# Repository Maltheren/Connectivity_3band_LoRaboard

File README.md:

# Connectivity_3band_LoRaboard
The first revision lora testboards for the tunnel measurement project

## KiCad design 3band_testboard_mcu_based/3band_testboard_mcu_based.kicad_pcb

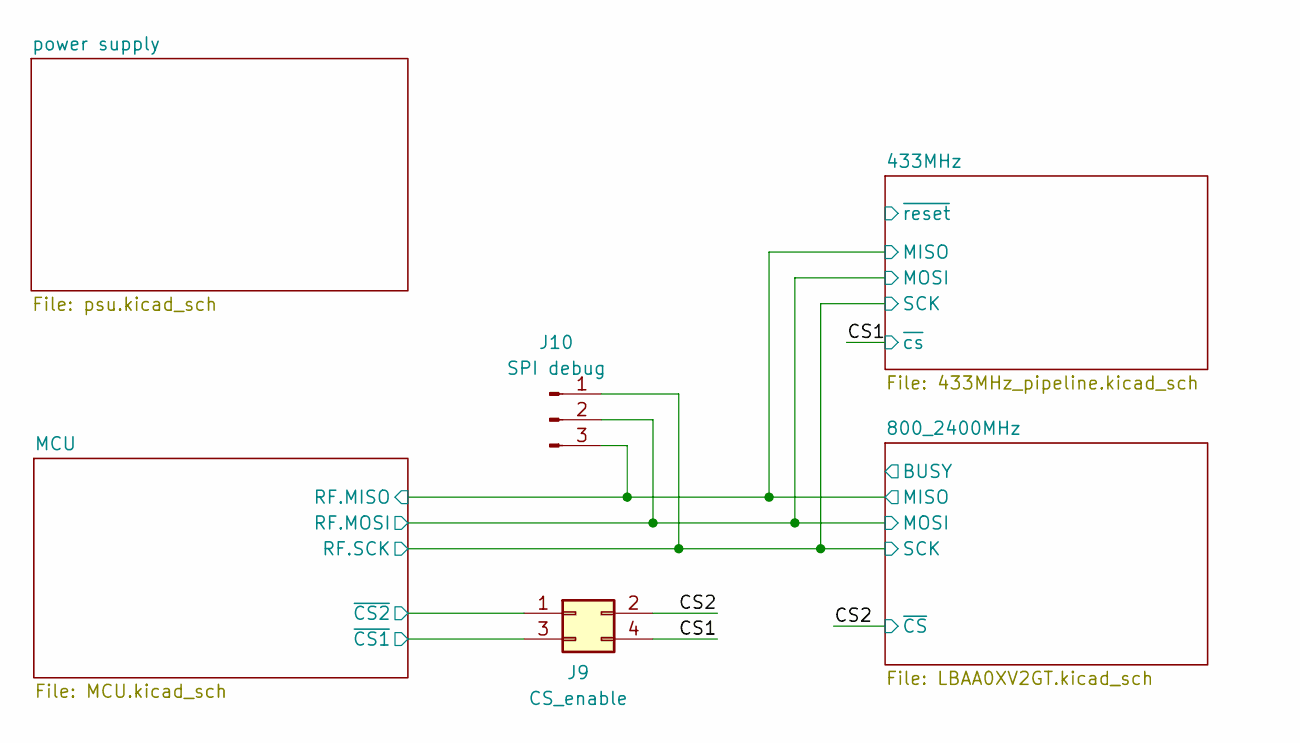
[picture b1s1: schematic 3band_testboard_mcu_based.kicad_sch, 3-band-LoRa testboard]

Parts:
J9: CS_enable; PinHeader_2x02_P2.54mm_Vertical
J10: SPI debug; PinHeader_1x03_P2.54mm_Vertical

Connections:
/433MHz/MISO: J10.3; also elsewhere on the board
/433MHz/MOSI: J10.2; also elsewhere on the board
/433MHz/SCK: J10.1; also elsewhere on the board
/CS1: J9.4; also elsewhere on the board
/CS2: J9.2; also elsewhere on the board
/MCU/~CS1: J9.3; also elsewhere on the board
/MCU/~CS2: J9.1; also elsewhere on the board

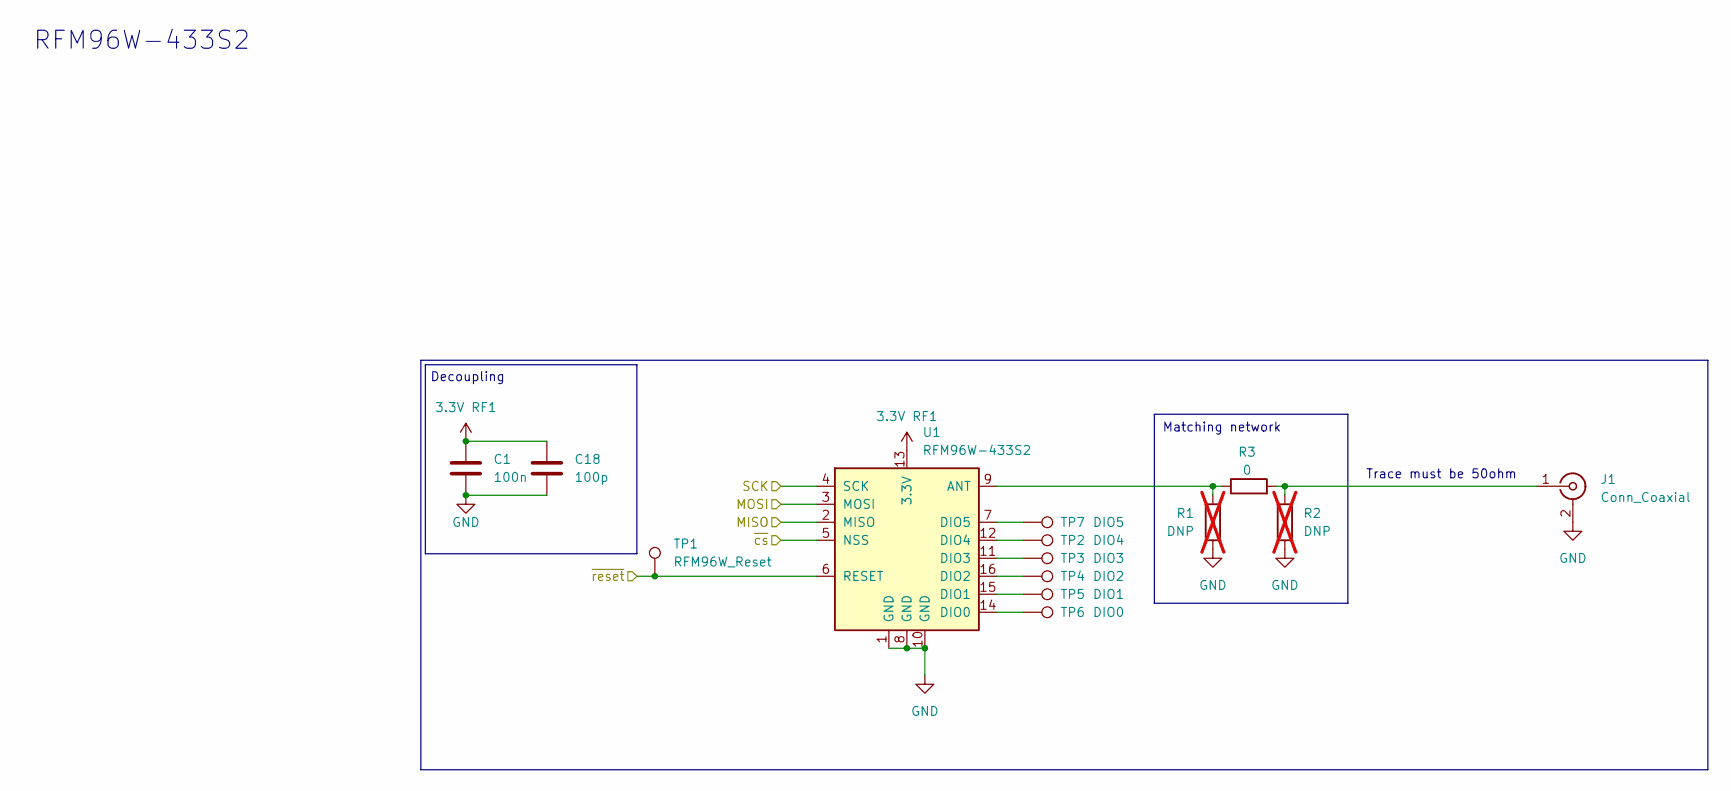
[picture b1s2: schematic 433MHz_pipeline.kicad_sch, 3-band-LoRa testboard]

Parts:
C1: 100n; C_0603_1608Metric_Pad1.08x0.95mm_HandSolder
C18: 100p; C_0603_1608Metric_Pad1.08x0.95mm_HandSolder
J1: Conn_Coaxial; SMA_Samtec_SMA-J-P-H-ST-EM1_EdgeMount
R1, R2: DNP; R_0603_1608Metric_Pad0.98x0.95mm_HandSolder; not fitted
R3: 0; R_0603_1608Metric_Pad0.98x0.95mm_HandSolder
TP1: RFM96W_Reset; TestPoint_Pad_D1.5mm
TP2: DIO4; TestPoint_Pad_D1.5mm
TP3: DIO3; TestPoint_Pad_D1.5mm
TP4: DIO2; TestPoint_Pad_D1.5mm
TP5: DIO1; TestPoint_Pad_D1.5mm
TP6: DIO0; TestPoint_Pad_D1.5mm
TP7: DIO5; TestPoint_Pad_D1.5mm
U1: RFM96W-433S2; HOPERF_RFM9XW_SMD

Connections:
3.3V RF1: C1.1, C18.1, U1.13 (3.3V); also elsewhere on the board
/433MHz/MISO: U1.2 (MISO); also elsewhere on the board
/433MHz/MOSI: U1.3 (MOSI); also elsewhere on the board
/433MHz/SCK: U1.4 (SCK); also elsewhere on the board
/433MHz/~reset: TP1.1, U1.6 (RESET)
/CS1: U1.5 (NSS); also elsewhere on the board
GND: C1.2, C18.2, J1.2 (Ext), R1.2, R2.2, U1.1 (GND), U1.8 (GND), U1.10 (GND); also elsewhere on the board
unnamed: J1.1 (In), R2.1, R3.2
unnamed: R1.1, R3.1, U1.9 (ANT)
unnamed: TP6.1, U1.14 (DIO0)
unnamed: TP5.1, U1.15 (DIO1)
unnamed: TP4.1, U1.16 (DIO2)
unnamed: TP3.1, U1.11 (DIO3)
unnamed: TP2.1, U1.12 (DIO4)
unnamed: TP7.1, U1.7 (DIO5)

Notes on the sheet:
RFM96W-433S2
Matching network
Trace must be 50ohm
Decoupling

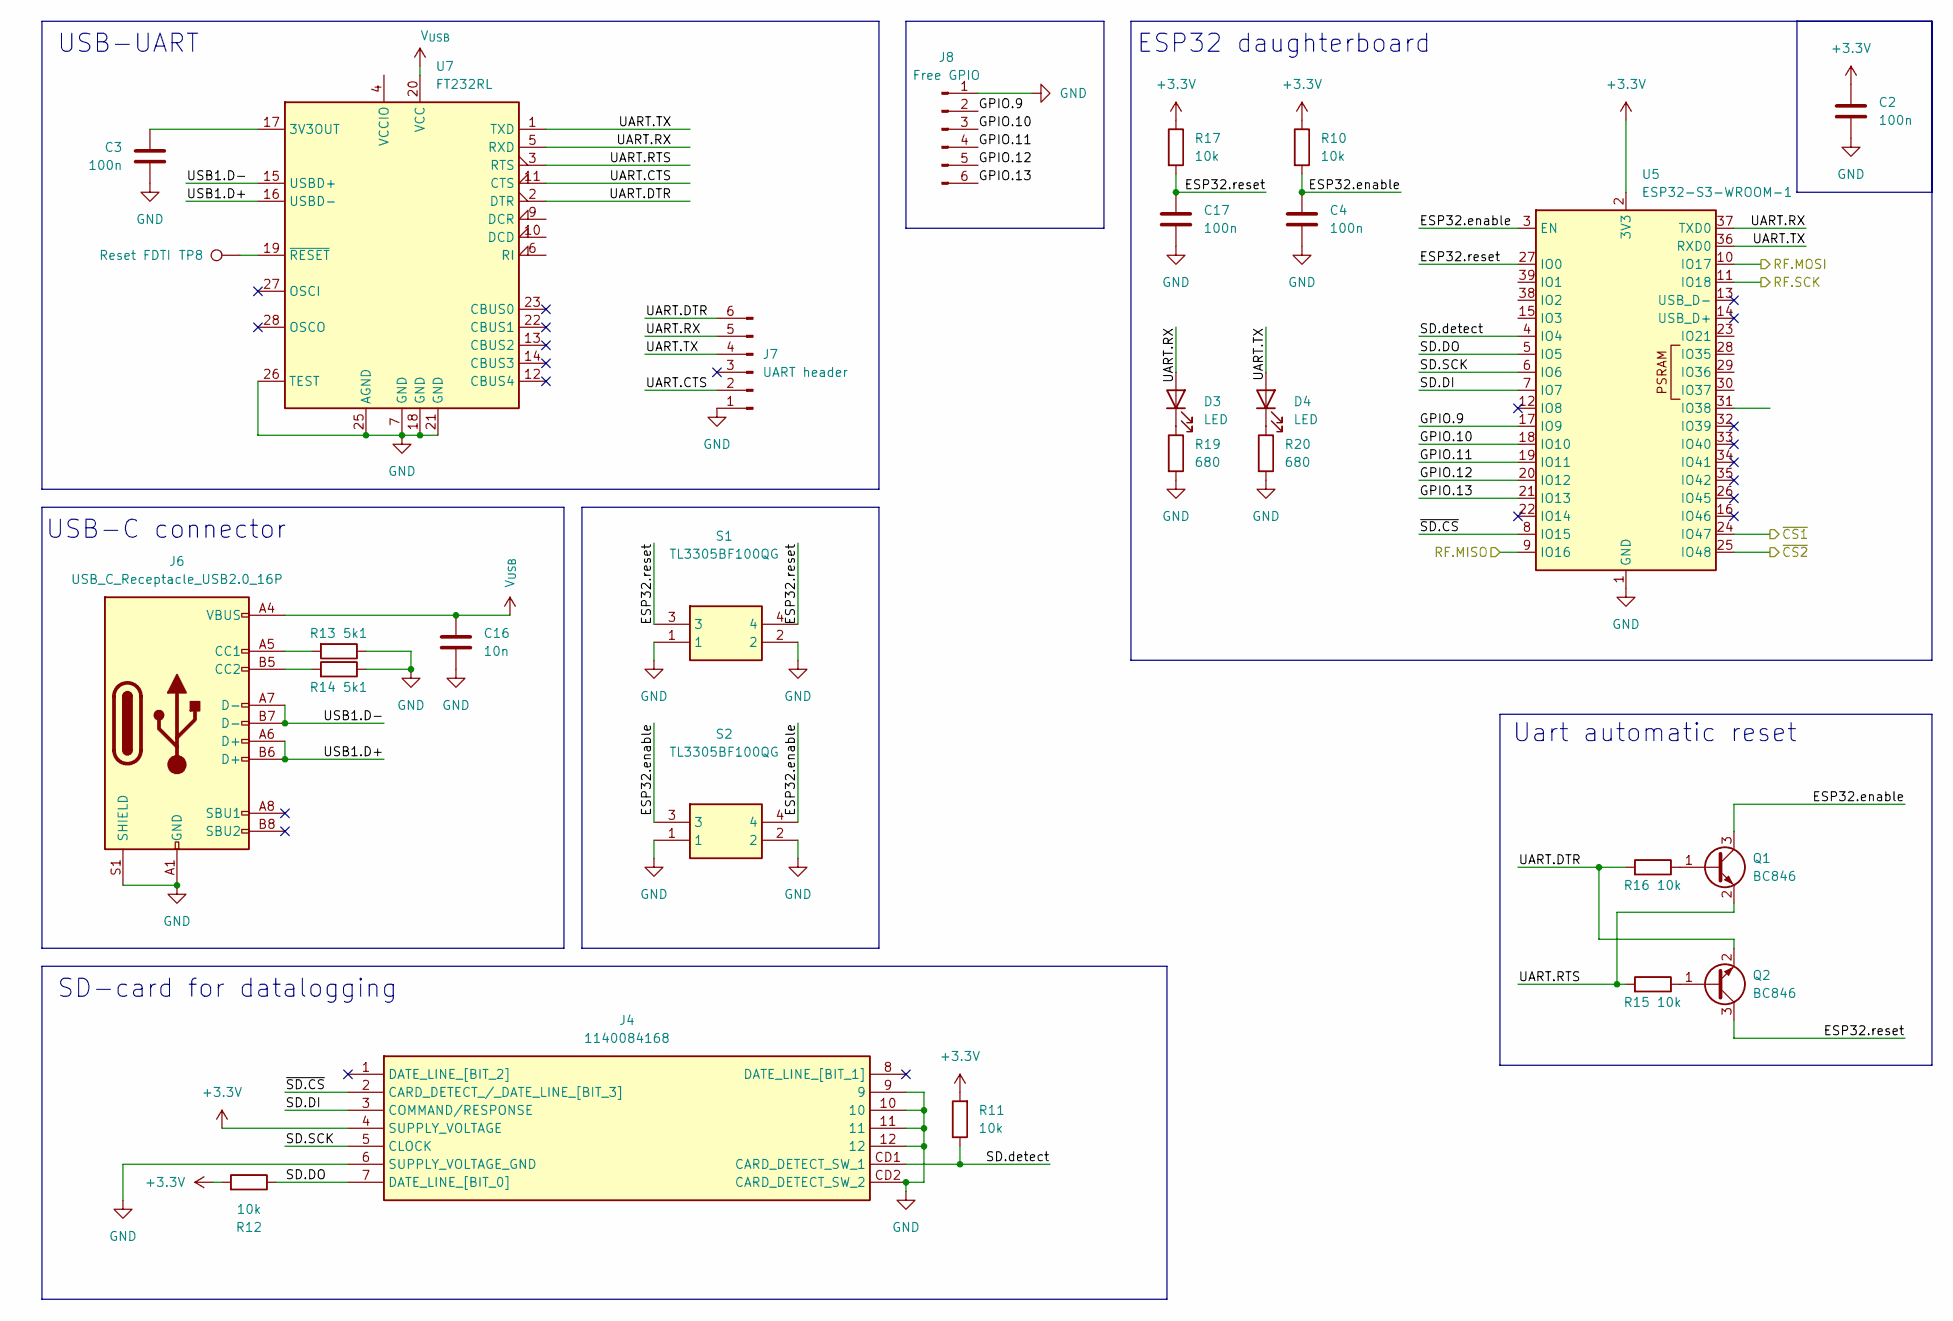
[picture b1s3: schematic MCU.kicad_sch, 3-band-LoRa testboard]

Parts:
C2, C3, C4, C17: 100n; C_0603_1608Metric
C16: 10n; C_0603_1608Metric
D3, D4: LED; LED_0603_1608Metric_Pad1.05x0.95mm_HandSolder
J4: 1140084168; Manufacturer_Part_Number 1140084168; Mouser Part Number 523-114-00841-68
J6: USB_C_Receptacle_USB2.0_16P; USB_C_Receptacle_HRO_TYPE-C-31-M-12
J7: UART header; PinSocket_1x06_P2.54mm_Vertical
J8: Free GPIO; PinHeader_1x06_P2.54mm_Vertical
Q1, Q2: BC846; SOT-23
R10, R11, R12, R15, R16, R17: 10k; R_0603_1608Metric
R13, R14: 5k1; R_0603_1608Metric
R19, R20: 680; R_0603_1608Metric
S1, S2: TL3305BF100QG; TL3305BF160QG; Mouser Part Number 612-TL3305BF100QG
TP8: Reset FDTI; TestPoint_Pad_D1.5mm
U5: ESP32-S3-WROOM-1
U7: FT232RL; SSOP-28_5.3x10.2mm_P0.65mm

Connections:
+3.3V: C2.1, J4.4 (SUPPLY_VOLTAGE), R10.1, R11.2, R12.2, R17.1, U5.2 (3V3); also elsewhere on the board
/433MHz/MISO: U5.9 (IO16); also elsewhere on the board
/433MHz/MOSI: U5.10 (IO17); also elsewhere on the board
/433MHz/SCK: U5.11 (IO18); also elsewhere on the board
/MCU/ESP32.enable: C4.1, Q1.3 (C), R10.2, S2.3, S2.4, U5.3 (EN)
/MCU/ESP32.reset: C17.1, Q2.3 (C), R17.2, S1.3, S1.4, U5.27 (IO0)
/MCU/GPIO.9: J8.2, U5.17 (IO9)
/MCU/GPIO.10: J8.3, U5.18 (IO10)
/MCU/GPIO.11: J8.4, U5.19 (IO11)
/MCU/GPIO.12: J8.5, U5.20 (IO12)
/MCU/GPIO.13: J8.6, U5.21 (IO13)
/MCU/SD.DI: J4.3 (COMMAND/RESPONSE), U5.7 (IO7)
/MCU/SD.DO: J4.7 (DATE_LINE_[BIT_0]), R12.1, U5.5 (IO5)
/MCU/SD.SCK: J4.5 (CLOCK), U5.6 (IO6)
/MCU/SD.detect: J4.CD1 (CARD_DETECT_SW_1), R11.1, U5.4 (IO4)
/MCU/UART.CTS: J7.2, U7.11 (CTS)
/MCU/UART.DTR: J7.6, Q2.2 (E), R16.2, U7.2 (DTR)
/MCU/UART.RTS: Q1.2 (E), R15.2, U7.3 (RTS)
/MCU/UART.RX: D3.2 (A), J7.5, U5.37 (TXD0), U7.5 (RXD)
/MCU/UART.TX: D4.2 (A), J7.4, U5.36 (RXD0), U7.1 (TXD)
/MCU/USB1.D+: J6.A6 (D+), J6.B6 (D+), U7.16 (USBD-)
/MCU/USB1.D-: J6.A7 (D-), J6.B7 (D-), U7.15 (USBD+)
/MCU/~CS1: U5.24 (IO47); also elsewhere on the board
/MCU/~CS2: U5.25 (IO48); also elsewhere on the board
/MCU/~SD.CS: J4.2 (CARD_DETECT_/_DATE_LINE_[BIT_3]), U5.8 (IO15)
GND: C2.2, C3.2, C4.2, C16.2, C17.2, J4.6 (SUPPLY_VOLTAGE_GND), J4.9, J4.10, J4.11, J4.12, J4.CD2 (CARD_DETECT_SW_2), J6.A1 (GND), J6.A12 (GND), J6.B1 (GND), J6.B12 (GND), J6.S1 (SHIELD), J7.1, J8.1, R13.1, R14.1, R19.2, R20.2, S1.1, S1.2, S2.1, S2.2, U5.1 (GND), U5.40 (GND), U5.41 (GND), U7.7 (GND), U7.18 (GND), U7.21 (GND), U7.25 (AGND), U7.26 (TEST); also elsewhere on the board
unnamed: D3.1 (K), R19.1
unnamed: D4.1 (K), R20.1
unnamed: J6.A5 (CC1), R13.2
unnamed: J6.B5 (CC2), R14.2
unnamed: Q1.1 (B), R16.1
unnamed: Q2.1 (B), R15.1
unnamed: C3.1, U7.17 (3V3OUT)
unnamed: TP8.1, U7.19 (~RESET)
V_{USB}: C16.1, J6.A4 (VBUS), J6.A9 (VBUS), J6.B4 (VBUS), J6.B9 (VBUS), U7.20 (VCC); also elsewhere on the board

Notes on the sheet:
USB-UART
USB-C connector
Uart automatic reset
SD-card for datalogging
ESP32 daughterboard

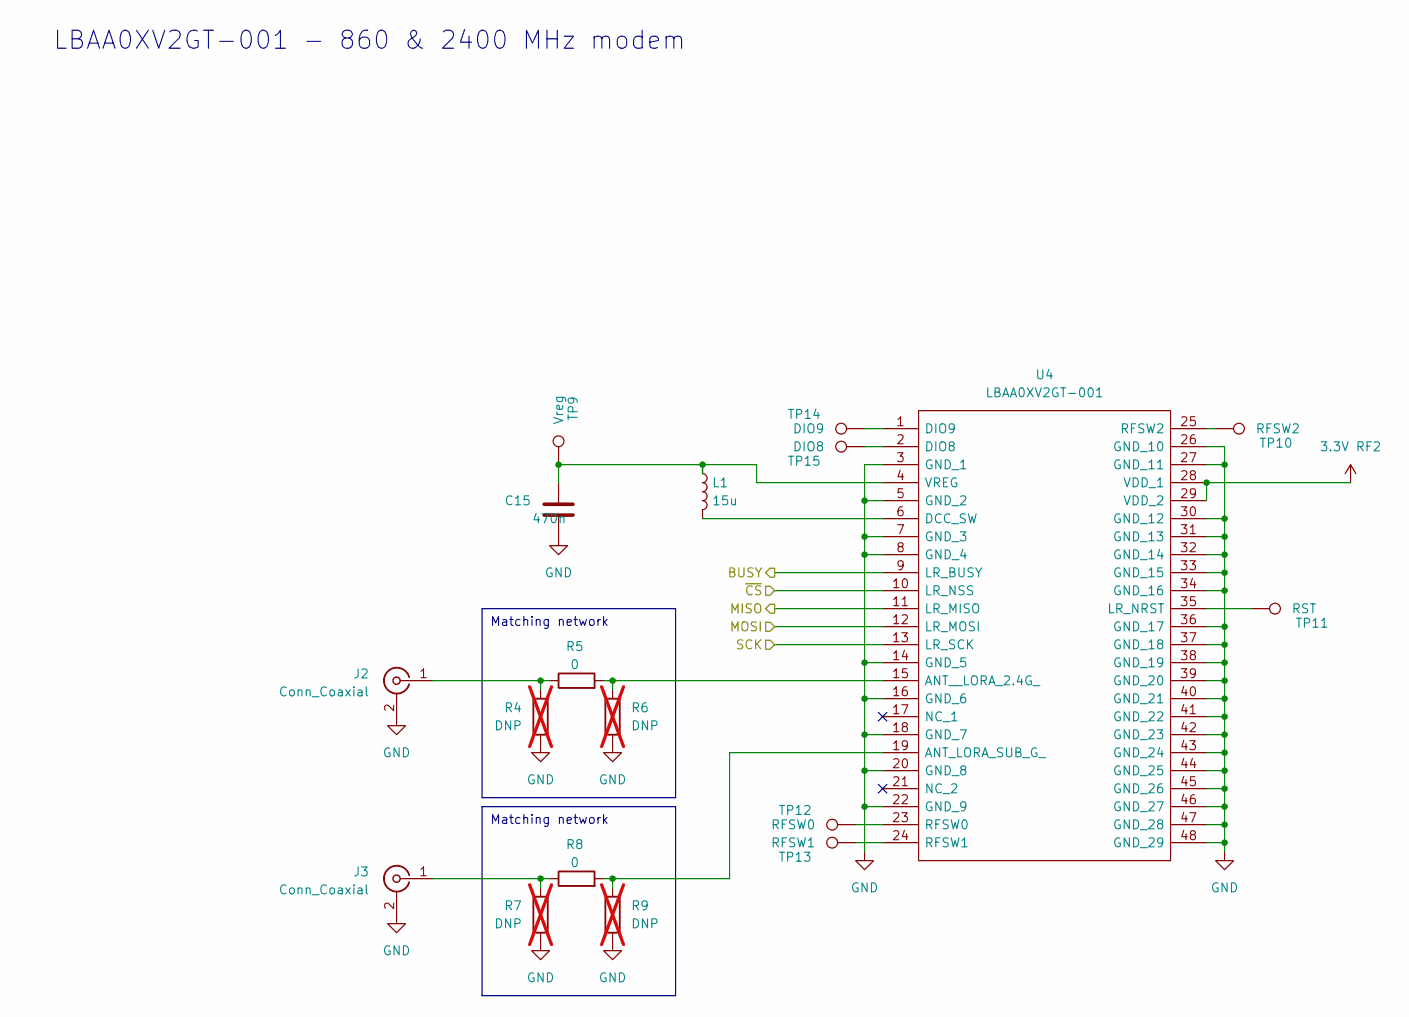
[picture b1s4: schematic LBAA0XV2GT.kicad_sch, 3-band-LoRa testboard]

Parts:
C15: 470n; C_0805_2012Metric_Pad1.18x1.45mm_HandSolder
J2, J3: Conn_Coaxial; SMA_Samtec_SMA-J-P-H-ST-EM1_EdgeMount
L1: 15u; ASPI-4030S
R4, R6, R7, R9: DNP; R_0603_1608Metric_Pad0.98x0.95mm_HandSolder; not fitted
R5, R8: 0; R_0603_1608Metric_Pad0.98x0.95mm_HandSolder
TP9: Vreg; TestPoint_Pad_D1.5mm
TP10: RFSW2; TestPoint_Pad_D1.5mm
TP11: RST; TestPoint_Pad_D1.5mm
TP12: RFSW0; TestPoint_Pad_D1.5mm
TP13: RFSW1; TestPoint_Pad_D1.5mm
TP14: DIO9; TestPoint_Pad_D1.5mm
TP15: DIO8; TestPoint_Pad_D1.5mm
U4: LBAA0XV2GT-001; LBAA0XV2GT001; Manufacturer_Part_Number LBAA0XV2GT-001

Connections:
3.3V RF2: U4.28 (VDD_1), U4.29 (VDD_2); also elsewhere on the board
/433MHz/MISO: U4.11 (LR_MISO); also elsewhere on the board
/433MHz/MOSI: U4.12 (LR_MOSI); also elsewhere on the board
/433MHz/SCK: U4.13 (LR_SCK); also elsewhere on the board
/800_2400MHz/BUSY: U4.9 (LR_BUSY)
/CS2: U4.10 (LR_NSS); also elsewhere on the board
GND: C15.1, J2.2 (Ext), J3.2 (Ext), R4.2, R6.2, R7.2, R9.2, U4.3 (GND_1), U4.5 (GND_2), U4.7 (GND_3), U4.8 (GND_4), U4.14 (GND_5), U4.16 (GND_6), U4.18 (GND_7), U4.20 (GND_8), U4.22 (GND_9), U4.26 (GND_10), U4.27 (GND_11), U4.30 (GND_12), U4.31 (GND_13), U4.32 (GND_14), U4.33 (GND_15), U4.34 (GND_16), U4.36 (GND_17), U4.37 (GND_18), U4.38 (GND_19), U4.39 (GND_20), U4.40 (GND_21), U4.41 (GND_22), U4.42 (GND_23), U4.43 (GND_24), U4.44 (GND_25), U4.45 (GND_26), U4.46 (GND_27), U4.47 (GND_28), U4.48 (GND_29); also elsewhere on the board
unnamed: J2.1 (In), R4.1, R5.1
unnamed: J3.1 (In), R7.1, R8.1
unnamed: R8.2, R9.1, U4.19 (ANT_LORA_SUB_G_)
unnamed: R5.2, R6.1, U4.15 (ANT__LORA_2.4G_)
unnamed: L1.2, U4.6 (DCC_SW)
unnamed: TP15.1, U4.2 (DIO8)
unnamed: TP14.1, U4.1 (DIO9)
unnamed: TP11.1, U4.35 (LR_NRST)
unnamed: TP12.1, U4.23 (RFSW0)
unnamed: TP13.1, U4.24 (RFSW1)
unnamed: TP10.1, U4.25 (RFSW2)
unnamed: C15.2, L1.1, TP9.1, U4.4 (VREG)

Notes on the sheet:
LBAA0XV2GT-001 - 860 & 2400 MHz modem
Matching network

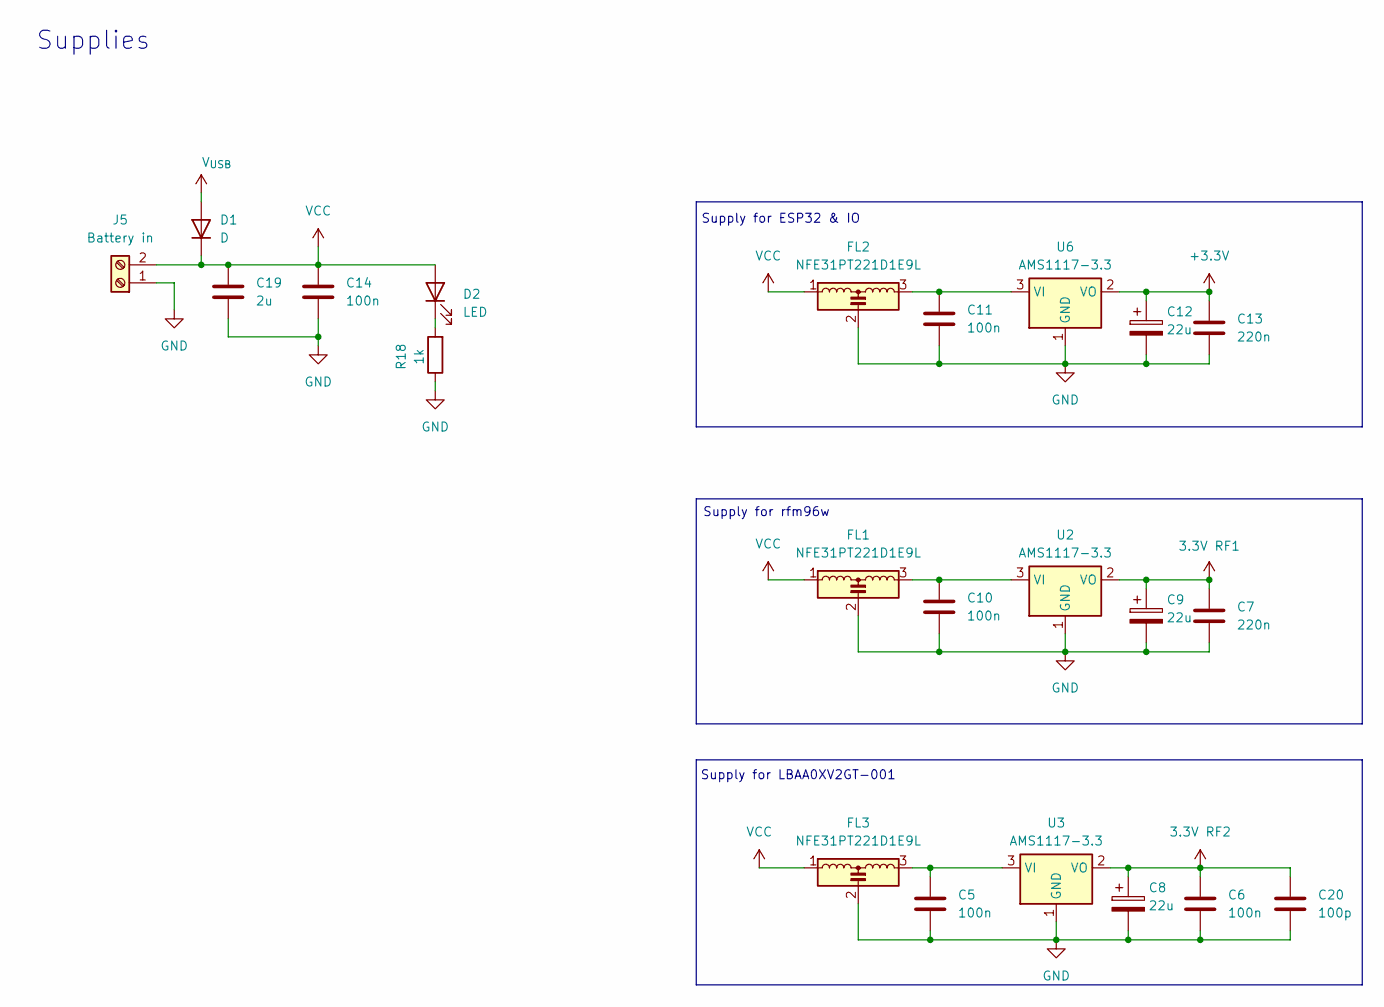
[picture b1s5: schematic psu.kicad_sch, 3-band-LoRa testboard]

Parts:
C5, C6, C10, C11, C14: 100n; C_0603_1608Metric
C7, C13: 220n; C_0603_1608Metric
C8, C9, C12: 22u; CP_Radial_D5.0mm_P2.50mm
C19: 2u; C_1206_3216Metric_Pad1.33x1.80mm_HandSolder
C20: 100p; C_0603_1608Metric
D1: D; D_SOD-323_HandSoldering
D2: LED; LED_D3.0mm
FL1, FL2, FL3: NFE31PT221D1E9L; Resonator_SMD_Murata_CSTxExxV-3Pin_3.0x1.1mm_HandSoldering
J5: Battery in; TerminalBlock_RND_205-00012_1x02_P5.00mm_Horizontal
R18: 1k; R_0603_1608Metric_Pad0.98x0.95mm_HandSolder
U2, U3, U6: AMS1117-3.3; SOT-223-3_TabPin2

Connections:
3.3V RF1: C7.1, C9.1, U2.2 (VO); also elsewhere on the board
3.3V RF2: C6.1, C8.1, C20.1, U3.2 (VO); also elsewhere on the board
+3.3V: C12.1, C13.1, U6.2 (VO); also elsewhere on the board
GND: C5.2, C6.2, C7.2, C8.2, C9.2, C10.2, C11.2, C12.2, C13.2, C14.2, C19.2, C20.2, FL1.2, FL2.2, FL3.2, J5.1, R18.1, U2.1 (GND), U3.1 (GND), U6.1 (GND); also elsewhere on the board
unnamed: D2.1 (K), R18.2
unnamed: C10.1, FL1.3, U2.3 (VI)
unnamed: C5.1, FL3.3, U3.3 (VI)
unnamed: C11.1, FL2.3, U6.3 (VI)
VCC: C14.1, C19.1, D1.1 (K), D2.2 (A), FL1.1, FL2.1, FL3.1, J5.2
V_{USB}: D1.2 (A); also elsewhere on the board

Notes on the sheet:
Supplies
Supply for ESP32 & IO
Supply for rfm96w
Supply for LBAA0XV2GT-001

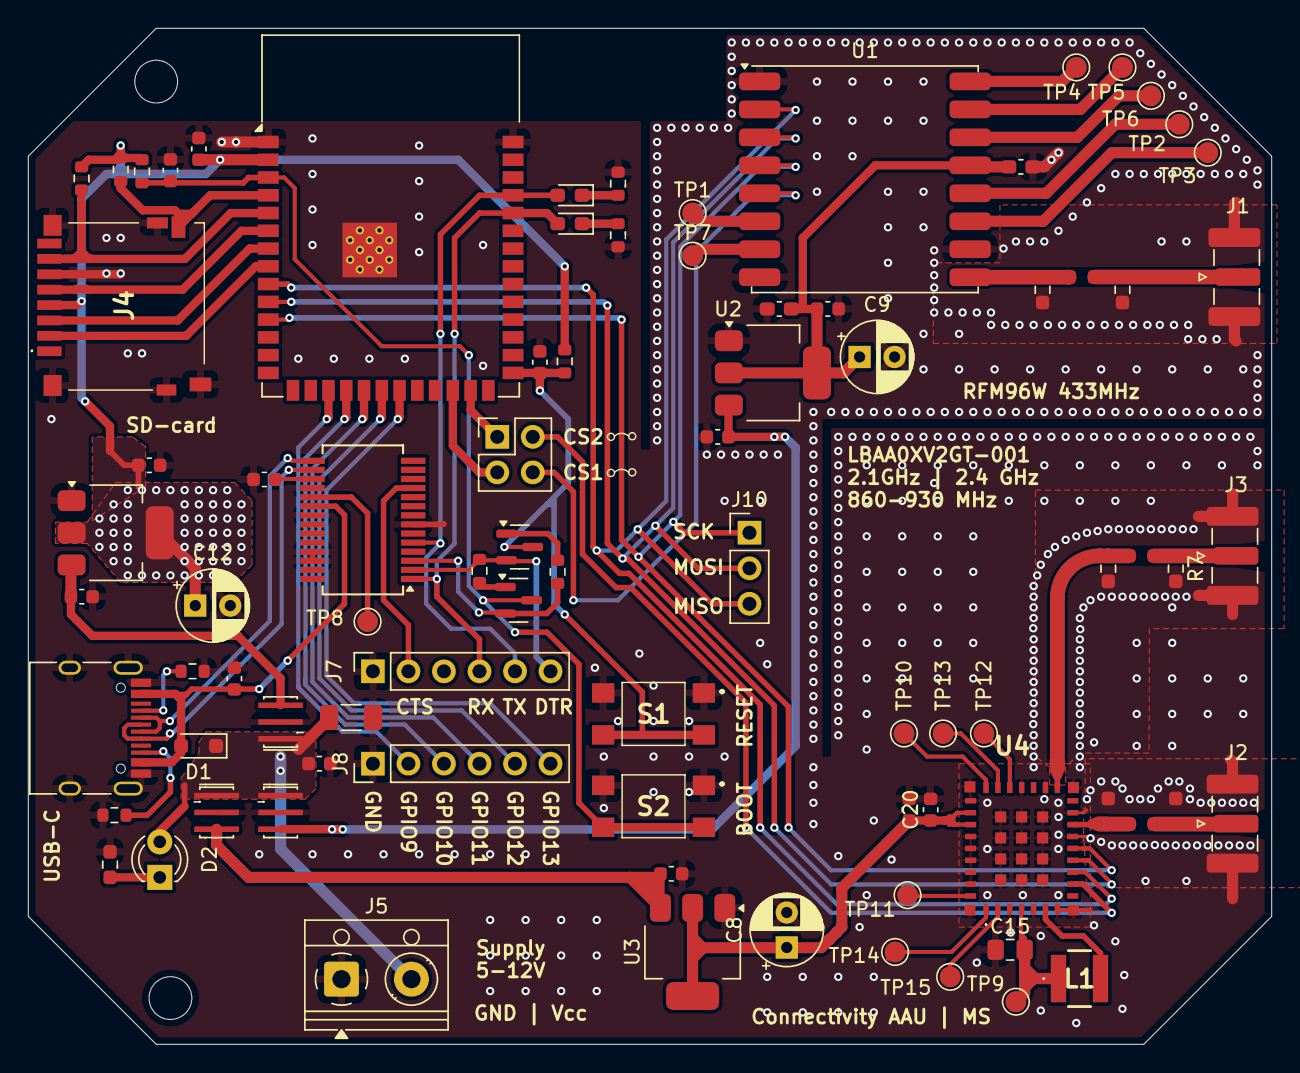
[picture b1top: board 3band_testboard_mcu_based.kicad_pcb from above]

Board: 2 copper layers, 88.9 x 72.6 mm, 84 parts (0 on the bottom side), 65 nets.

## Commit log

2025-03-31 Inital commit
2025-04-04 Færdiggjorde GPIO
2025-04-08 DRC check, and price
2025-04-10 Prisoverslag
2025-04-29 Drivers and code
2025-05-11 nothing works
2025-09-18 various measurements
2025-09-18 The SW used by RX and TX
